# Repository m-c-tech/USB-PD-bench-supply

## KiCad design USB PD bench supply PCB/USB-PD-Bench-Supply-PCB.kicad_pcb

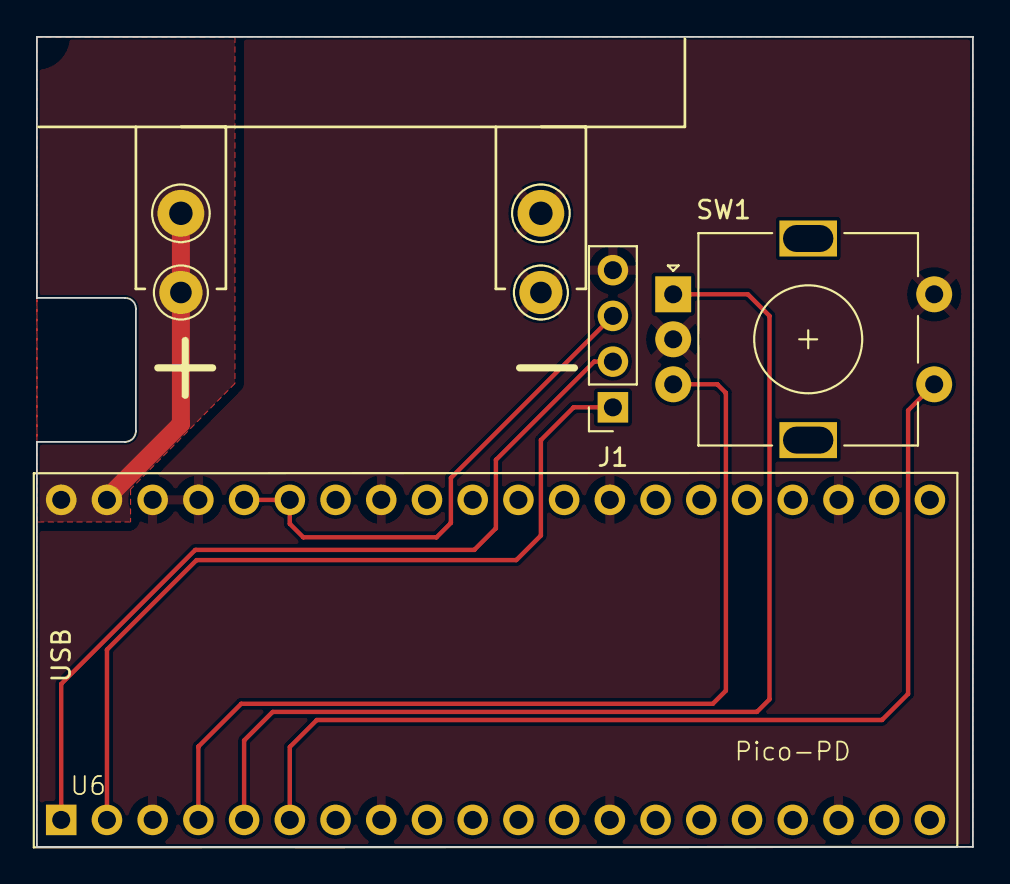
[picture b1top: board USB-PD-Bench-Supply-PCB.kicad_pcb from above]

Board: 2 copper layers, 52.0 x 45.0 mm, 7 parts (0 on the bottom side), 8 nets.

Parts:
J1: Conn_01x04; PinSocket_1x04_P2.54mm_Vertical
J2, J4: Conn_01x01; Pin_D1.3mm_L11.0mm
J3, J5: Conn_01x01; Pin_D1.0mm_L10.0mm_LooseFit
SW1: RotaryEncoder_Switch; RotaryEncoder_Alps_EC11E-Switch_Vertical_H15mm
U6: Pico-PD

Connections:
+3V3: J1.3, U6.35 (3V3), U6.36 (3V3)
/ENC_A: SW1.A, U6.5 (GPIO3)
/ENC_B: SW1.B, U6.4 (GPIO2)
/ENC_SW: SW1.S1, U6.6 (GPIO4)
/SCL: J1.1, U6.2 (SCL_0)
/SDA: J1.2, U6.1 (SDA_0)
/VBUS: J2.1, J3.1, U6.39 (VBUS), U6.40 (VBUS)
GND: J1.4, J4.1, J5.1, SW1.C, SW1.S2, U6.3 (GND), U6.8 (GND), U6.13 (GND), U6.18 (GND), U6.23 (GND), U6.28 (GND), U6.33 (GND), U6.37 (GND), U6.38 (GND)

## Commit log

2023-12-18 Update PD_Supply_with_encoder.ino
    Initial commit had an old version
2023-12-20 Updated after receiving all parts
    enclosure updated
    changed folder structure to suit Arduino IDE
    screen layout modified
2024-03-23 Modified screen layout
    Modified screen layout
